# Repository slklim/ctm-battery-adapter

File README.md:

# ctm-battery-adapter
Hardware solution to replace two AAA batteries used to power a handheld CTM device

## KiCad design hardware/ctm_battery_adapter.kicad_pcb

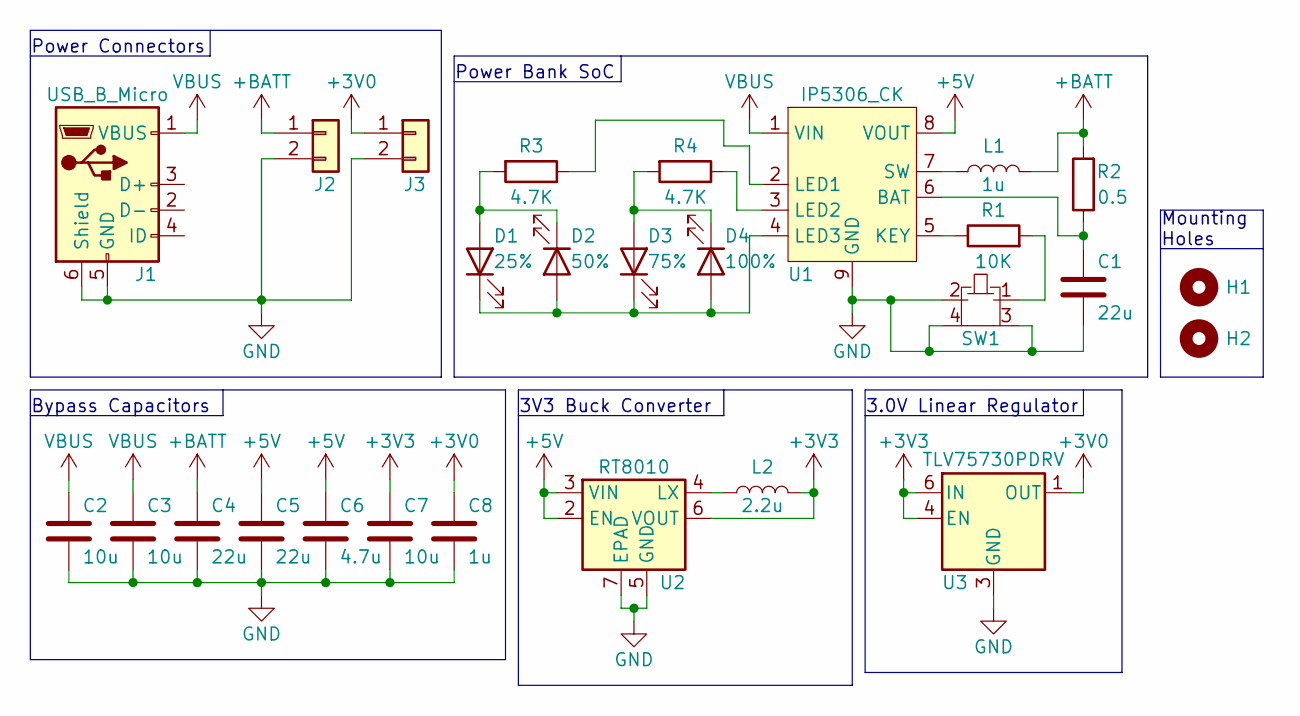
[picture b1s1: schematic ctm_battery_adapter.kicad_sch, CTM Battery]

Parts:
C1, C4, C5: 22u; C_0603_1608Metric
C2, C3, C7: 10u; C_0603_1608Metric
C6: 4.7u; C_0603_1608Metric
C8: 1u; C_0603_1608Metric
D1: 25%; LED_RA_0402
D2: 50%; LED_RA_0402
D3: 75%; LED_RA_0402
D4: 100%; LED_RA_0402
H1, H2: MountingHole; MountingHole_3.2mm_M3
J1: USB_B_Micro; USB_Micro-B_Amphenol_10118192_Horizontal
J2, J3: Conn_01x02; PinHeader_1x02_P2.54mm_Vertical
L1: 1u; L_Vishay_IHHP_0806ZH
L2: 2.2u; L_Vishay_IHHP_0806ZH
R1: 10K; R_0402_1005Metric
R2: 0.5; R_0603_1608Metric
R3, R4: 4.7K; R_0402_1005Metric
SW1: SW_Push_SPST_Shielded; SW_Tactile_SKHH_Angled_Shielded
U1: IP5306_CK; eSOP-8
U2: RT8010; WDFN-6L_2x2
U3: TLV75730PDRV; WSON-6_2x2

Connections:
+3V0: C8.1, J3.1, U3.1 (OUT)
+3V3: C7.1, L2.2, U2.6 (VOUT), U3.4 (EN), U3.6 (IN)
+5V: C5.1, C6.1, U1.8 (VOUT), U2.2 (EN), U2.3 (VIN)
+BATT: C4.1, J2.1, L1.2, R2.2
GND: C1.2, C2.2, C3.2, C4.2, C5.2, C6.2, C7.2, C8.2, J1.5 (GND), J1.6 (Shield), J2.2, J3.2, SW1.2 (B), SW1.3 (SH1), SW1.4 (SH2), U1.9 (GND), U2.5 (GND), U2.7 (EPAD), U3.3 (GND), U3.7 (GND)
unnamed: D1.2 (A), D2.1 (K), R3.2
unnamed: D1.1 (K), D2.2 (A), D3.1 (K), D4.2 (A), U1.4 (LED3)
unnamed: D3.2 (A), D4.1 (K), R4.2
unnamed: R1.2, SW1.1 (A)
unnamed: C1.1, R2.1, U1.6 (BAT)
unnamed: R1.1, U1.5 (KEY)
unnamed: R3.1, U1.2 (LED1)
unnamed: R4.1, U1.3 (LED2)
unnamed: L1.1, U1.7 (SW)
unnamed: L2.1, U2.4 (LX)
VBUS: C2.1, C3.1, J1.1 (VBUS), U1.1 (VIN)

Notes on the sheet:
Bypass Capacitors
Mounting Holes
Power Bank SoC
Power Connectors
3.0V Linear Regulator
3V3 Buck Converter

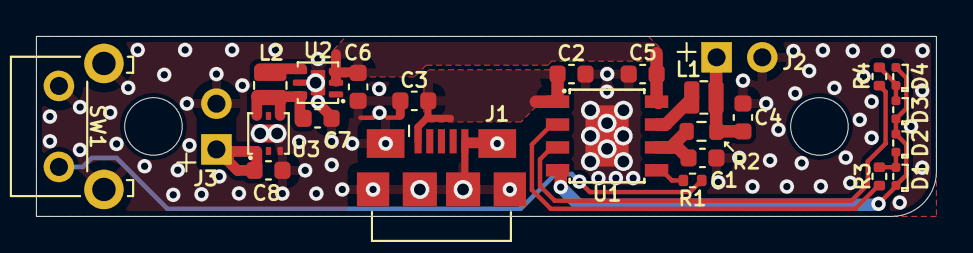
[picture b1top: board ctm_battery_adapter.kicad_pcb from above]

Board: 2 copper layers, 50.0 x 10.0 mm, 27 parts (0 on the bottom side), 16 nets.

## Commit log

2023-03-18 Add files via upload
    Final version sent to JPLPCB for fabrication and assembly
